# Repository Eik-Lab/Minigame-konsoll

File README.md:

# Minigame-konsoll
Dette repoet inneholder alt du trenger for å lage en minigame-konsoll. Prosjektet er en del av tre workshoper: 

* PCB  
* 3D-modellering og 3D-printing 
* Mikrokontrollere og sensorikk 

Innhold blir lagt ut forløpende!

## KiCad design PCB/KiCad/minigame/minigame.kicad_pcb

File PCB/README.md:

# PCB workshop

Workshopen handler om det grunnleggende innen kretsdesign og hvordan man designer en krets i KiCad. Som en del av minigame-konsoll prosjektet er PCB designet det første steget man tar for å lage produktet! 

Tips før du starter:
* Se gjennom "workshop_material/kræsjkurs_elektronikk.pdf" (Anbefalt hvis du ikke er helt sikker på elektronikk!)
* Se gjennom "workshop_material/PCB_workshop.pdf"
* Last ned KiCad 7.0

Fremgangsmetode for designprosessen i KiCad finner du i "PCB_tutorial.pdf".

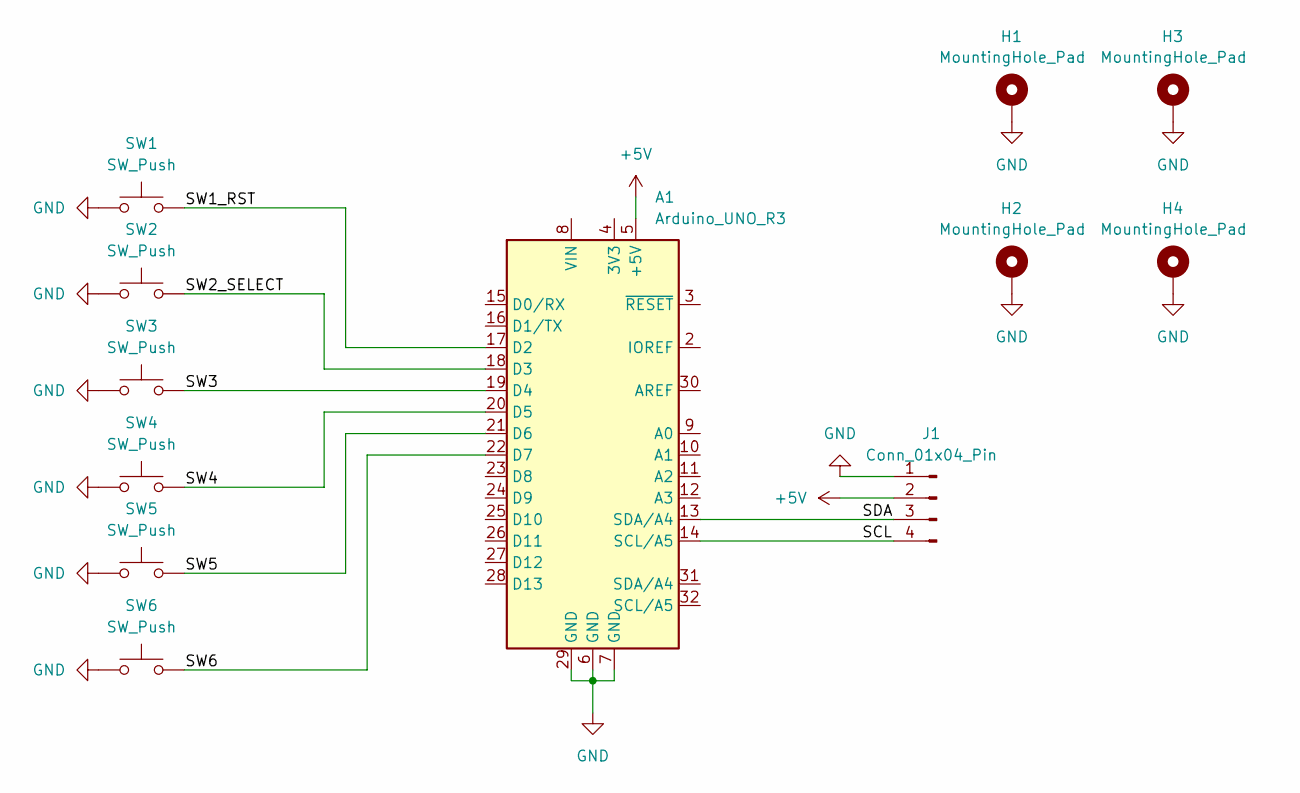
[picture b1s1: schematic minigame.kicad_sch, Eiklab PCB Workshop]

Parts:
A1: Arduino_UNO_R3
H1, H2, H3, H4: MountingHole_Pad; MountingHole_3mm_Pad_TopBottom
J1: Conn_01x04_Pin; PinHeader_1x04_P2.54mm_Vertical
SW1, SW2, SW3, SW4, SW5, SW6: SW_Push; SW_PUSH-12mm

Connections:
+5V: A1.5 (+5V), J1.2
/SCL: A1.14 (SCL/A5), J1.4
/SDA: A1.13 (SDA/A4), J1.3
/SW1_RST: A1.17 (D2), SW1.2
/SW2_SELECT: A1.18 (D3), SW2.2
/SW3: A1.19 (D4), SW3.2
/SW4: A1.20 (D5), SW4.2
/SW5: A1.21 (D6), SW5.2
/SW6: A1.22 (D7), SW6.2
GND: A1.6 (GND), A1.7 (GND), A1.29 (GND), H1.1, H2.1, H3.1, H4.1, J1.1, SW1.1, SW2.1, SW3.1, SW4.1, SW5.1, SW6.1

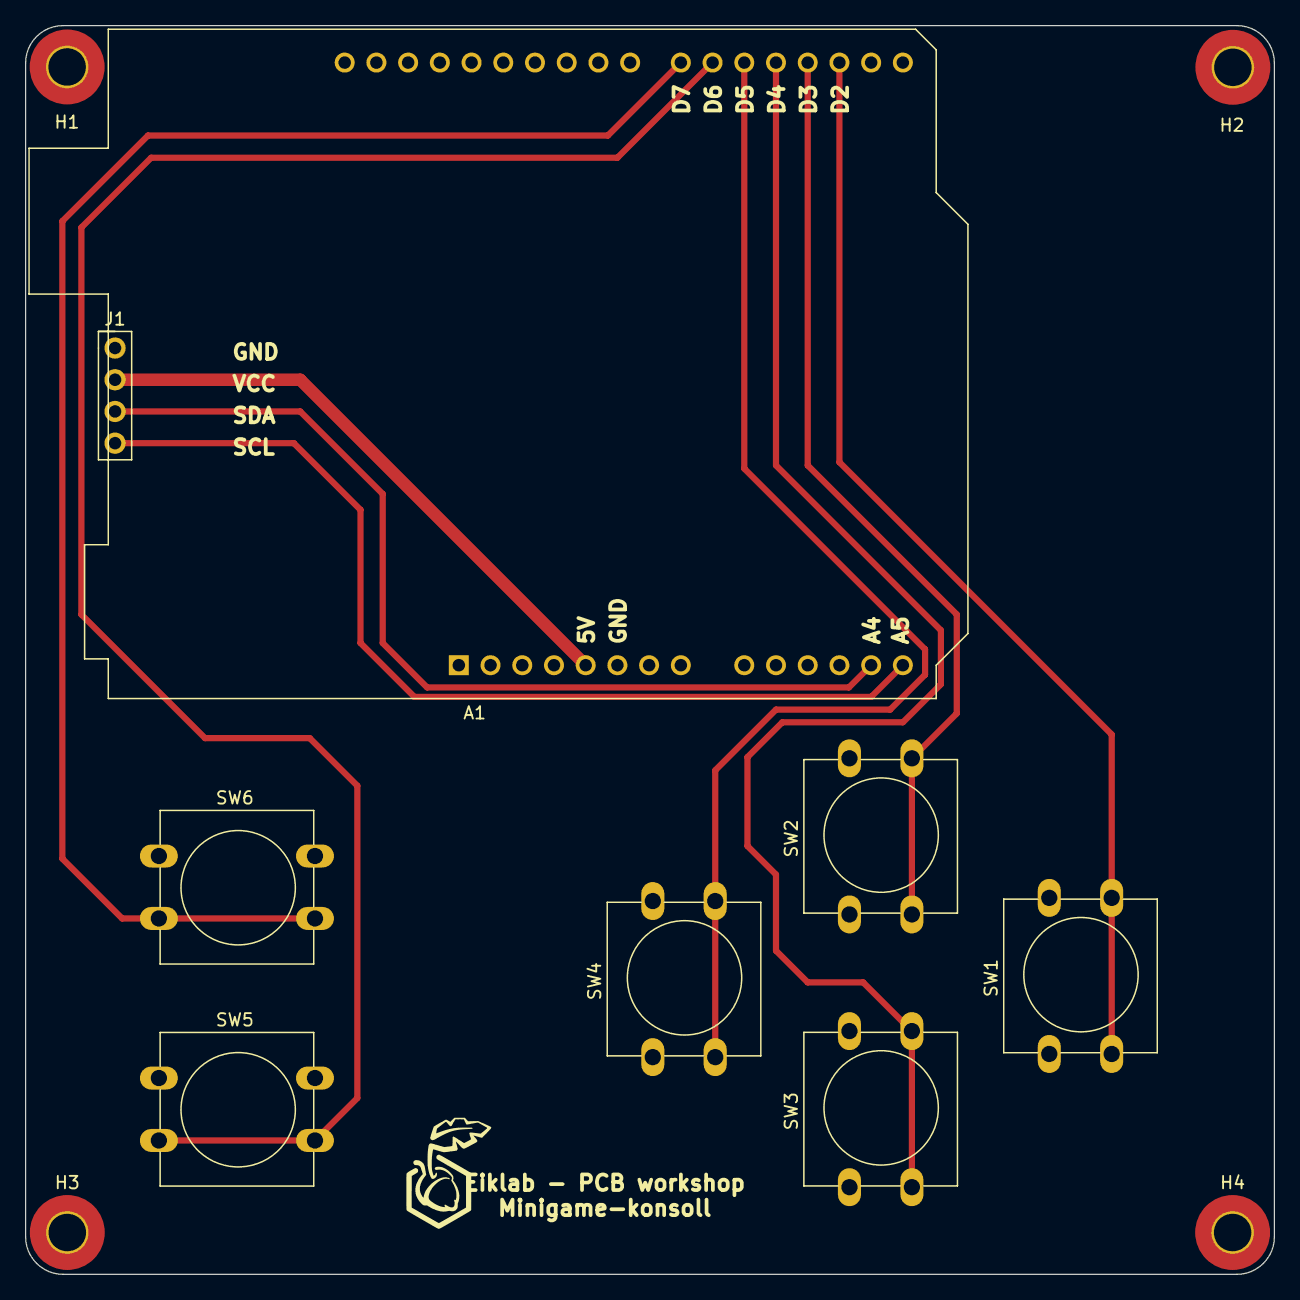
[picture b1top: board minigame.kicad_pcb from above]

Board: 2 copper layers, 100.0 x 100.0 mm, 12 parts (0 on the bottom side), 10 nets.

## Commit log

2024-02-12 feat: added map structure
2024-02-12 fix: updated PCB README.md
2024-02-12 feat: added reading material
2024-02-13 feat: added tutorial
2024-02-13 fix: updated README.md
2024-02-13 feat: added the presentation
2024-02-16 feat: added KiCad files and .gitignore
2024-02-17 feat: added 3D model and updated the PCB
2024-02-17 feat: added 3D model of PCB
2024-04-11 Added code for the project
2024-04-11 Update LCDML_control.ino
    changed the button layout to work with the assigned pcb layout
2024-04-11 Update Hangman_I2C.ino
    changed the button layout to work with the assigned pcb layout of the main file
